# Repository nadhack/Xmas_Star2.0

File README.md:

Design files and documentation for the NADHack Xmas Star V2.0 as used in 
the SMD soldering workshop 2025.

* Addons - Addon files, source  and reference designs to enhance your stars.
* Docs - Assembly documentation greated using [MkDocs](https://www.mkdocs.org/)
* Hardware - [KiCad](https://www.kicad.org/) design files.

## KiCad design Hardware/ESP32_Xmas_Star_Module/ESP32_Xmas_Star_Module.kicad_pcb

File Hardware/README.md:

Hardware files for the NADHack Xmas Star V2.0.

* ESP32_Xmas_Star_Module - [KiCad](https://www.kicad.org/) design files.
* Jigs - Source and 3D print files for holding star PCB while applying solderpaste.

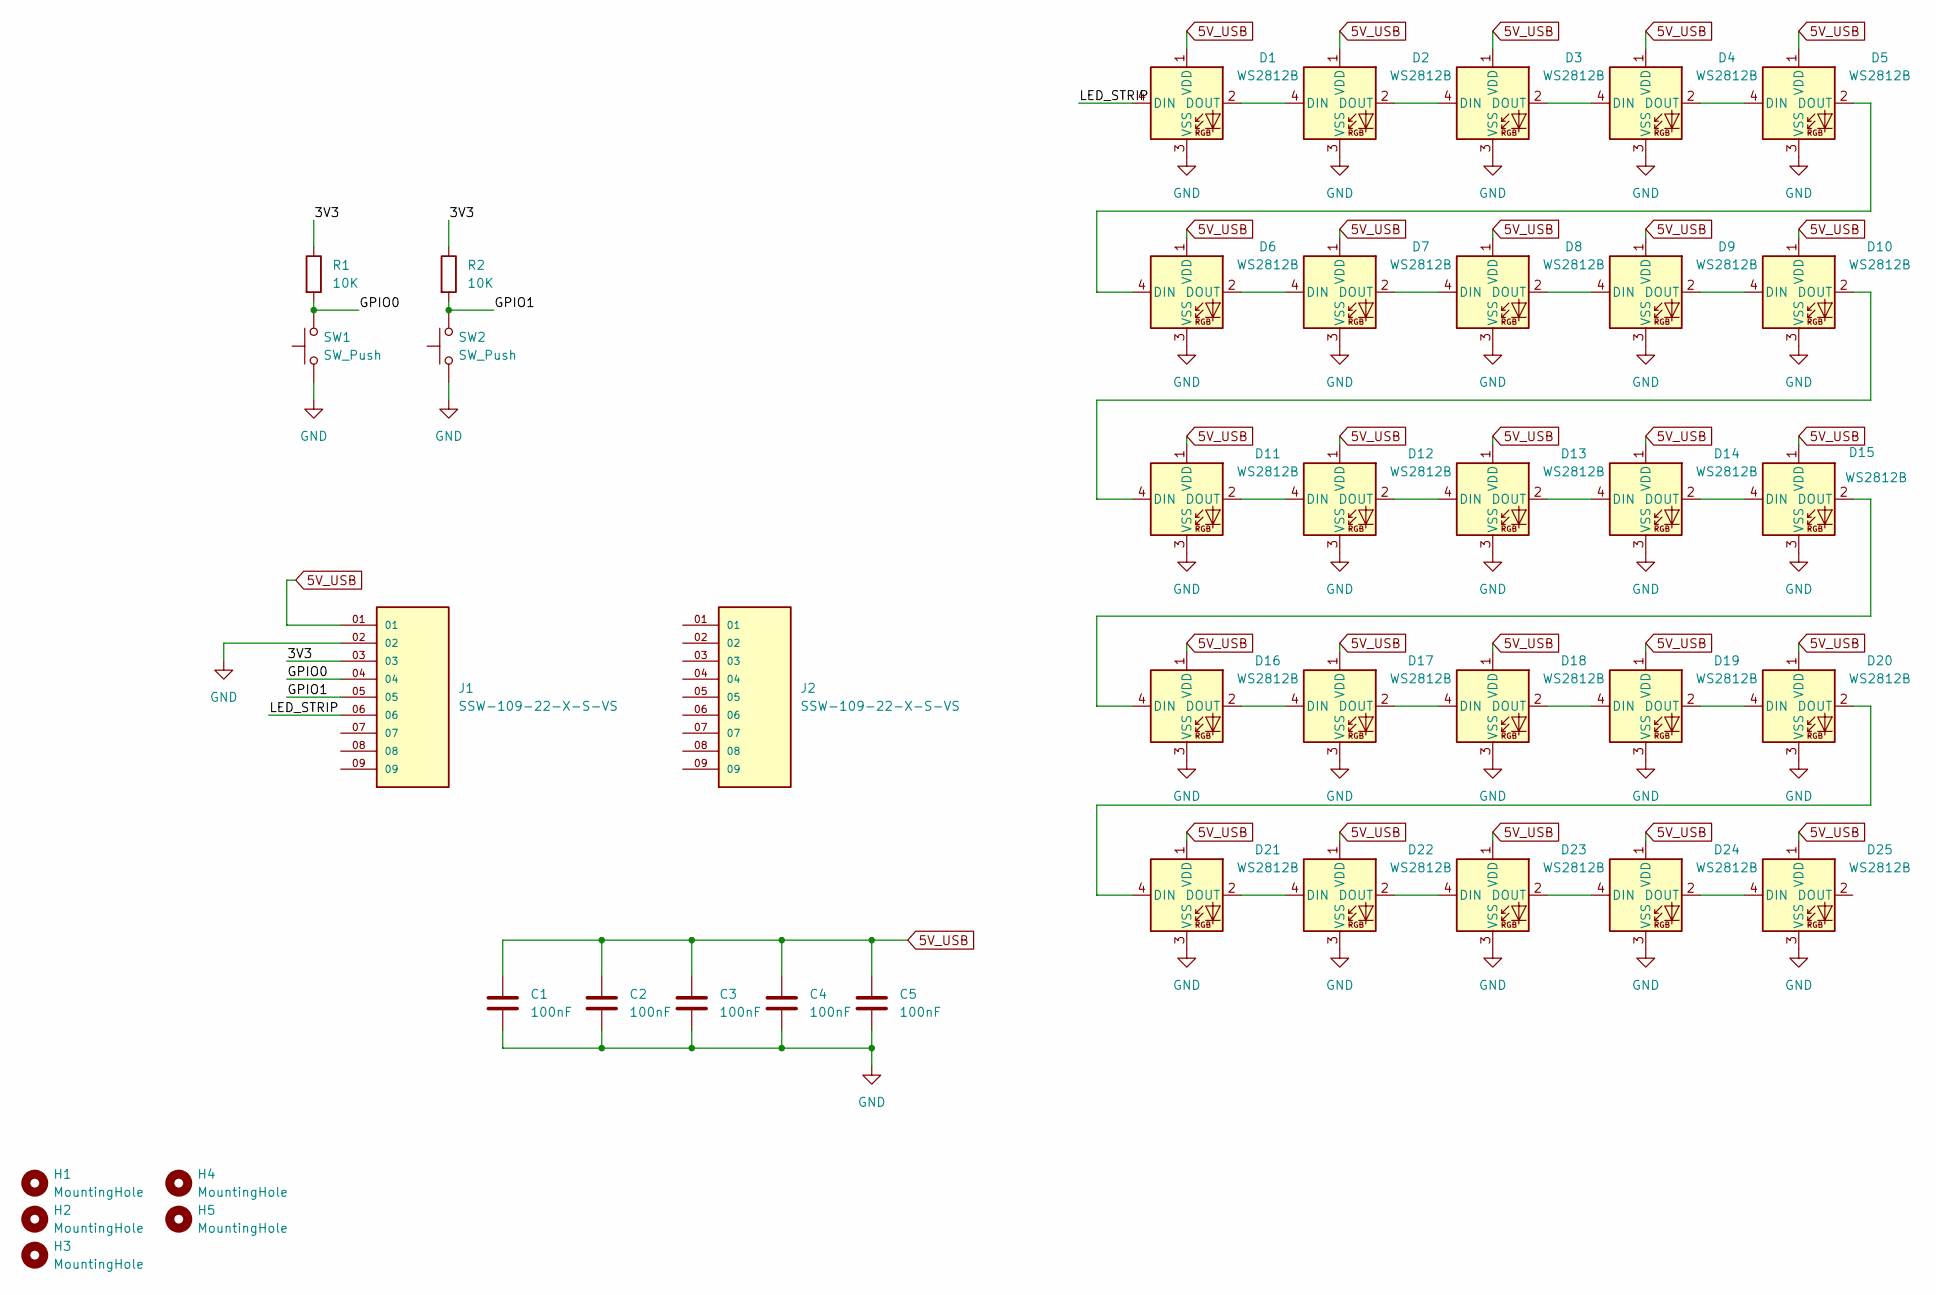
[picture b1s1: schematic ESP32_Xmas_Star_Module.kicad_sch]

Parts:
C1, C2, C3, C4, C5: 100nF; C_0805_2012Metric_Pad1.18x1.45mm_HandSolder
D1, D2, D3, D4, D5, D6, D7, D8, D9, D10, D11, D12, D13, D14, D15, D16, D17, D18, D19, D20, D21, D22, D23, D24, D25: WS2812B; LED_WS2812B_PLCC4_5.0x5.0mm_P3.2mm
H1, H2, H3, H4, H5: MountingHole; MountingHole_2.2mm_M2_Pad
J1, J2: SSW-109-22-X-S-VS; SAMTEC_SSW-109-22-X-S-VS; PARTREV B
R1, R2: 10K; R_0805_2012Metric_Pad1.20x1.40mm_HandSolder
SW1, SW2: SW_Push; SW_SPST_FSMSM

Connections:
5V_USB: C1.1, C2.1, C3.1, C4.1, C5.1, D1.1 (VDD), D2.1 (VDD), D3.1 (VDD), D4.1 (VDD), D5.1 (VDD), D6.1 (VDD), D7.1 (VDD), D8.1 (VDD), D9.1 (VDD), D10.1 (VDD), D11.1 (VDD), D12.1 (VDD), D13.1 (VDD), D14.1 (VDD), D15.1 (VDD), D16.1 (VDD), D17.1 (VDD), D18.1 (VDD), D19.1 (VDD), D20.1 (VDD), D21.1 (VDD), D22.1 (VDD), D23.1 (VDD), D24.1 (VDD), D25.1 (VDD), J1.01
/3V3: J1.03, R1.1, R2.1
/GPIO0: J1.04, R1.2, SW1.2
/GPIO1: J1.05, R2.2, SW2.2
/LED_STRIP: D1.4 (DIN), J1.06
GND: C1.2, C2.2, C3.2, C4.2, C5.2, D1.3 (VSS), D2.3 (VSS), D3.3 (VSS), D4.3 (VSS), D5.3 (VSS), D6.3 (VSS), D7.3 (VSS), D8.3 (VSS), D9.3 (VSS), D10.3 (VSS), D11.3 (VSS), D12.3 (VSS), D13.3 (VSS), D14.3 (VSS), D15.3 (VSS), D16.3 (VSS), D17.3 (VSS), D18.3 (VSS), D19.3 (VSS), D20.3 (VSS), D21.3 (VSS), D22.3 (VSS), D23.3 (VSS), D24.3 (VSS), D25.3 (VSS), J1.02, SW1.1, SW2.1
unnamed: D1.2 (DOUT), D2.4 (DIN)
unnamed: D2.2 (DOUT), D3.4 (DIN)
unnamed: D3.2 (DOUT), D4.4 (DIN)
unnamed: D4.2 (DOUT), D5.4 (DIN)
unnamed: D5.2 (DOUT), D6.4 (DIN)
unnamed: D6.2 (DOUT), D7.4 (DIN)
unnamed: D7.2 (DOUT), D8.4 (DIN)
unnamed: D8.2 (DOUT), D9.4 (DIN)
unnamed: D9.2 (DOUT), D10.4 (DIN)
unnamed: D10.2 (DOUT), D11.4 (DIN)
unnamed: D11.2 (DOUT), D12.4 (DIN)
unnamed: D12.2 (DOUT), D13.4 (DIN)
unnamed: D13.2 (DOUT), D14.4 (DIN)
unnamed: D14.2 (DOUT), D15.4 (DIN)
unnamed: D15.2 (DOUT), D16.4 (DIN)
unnamed: D16.2 (DOUT), D17.4 (DIN)
unnamed: D17.2 (DOUT), D18.4 (DIN)
unnamed: D18.2 (DOUT), D19.4 (DIN)
unnamed: D19.2 (DOUT), D20.4 (DIN)
unnamed: D20.2 (DOUT), D21.4 (DIN)
unnamed: D21.2 (DOUT), D22.4 (DIN)
unnamed: D22.2 (DOUT), D23.4 (DIN)
unnamed: D23.2 (DOUT), D24.4 (DIN)
unnamed: D24.2 (DOUT), D25.4 (DIN)

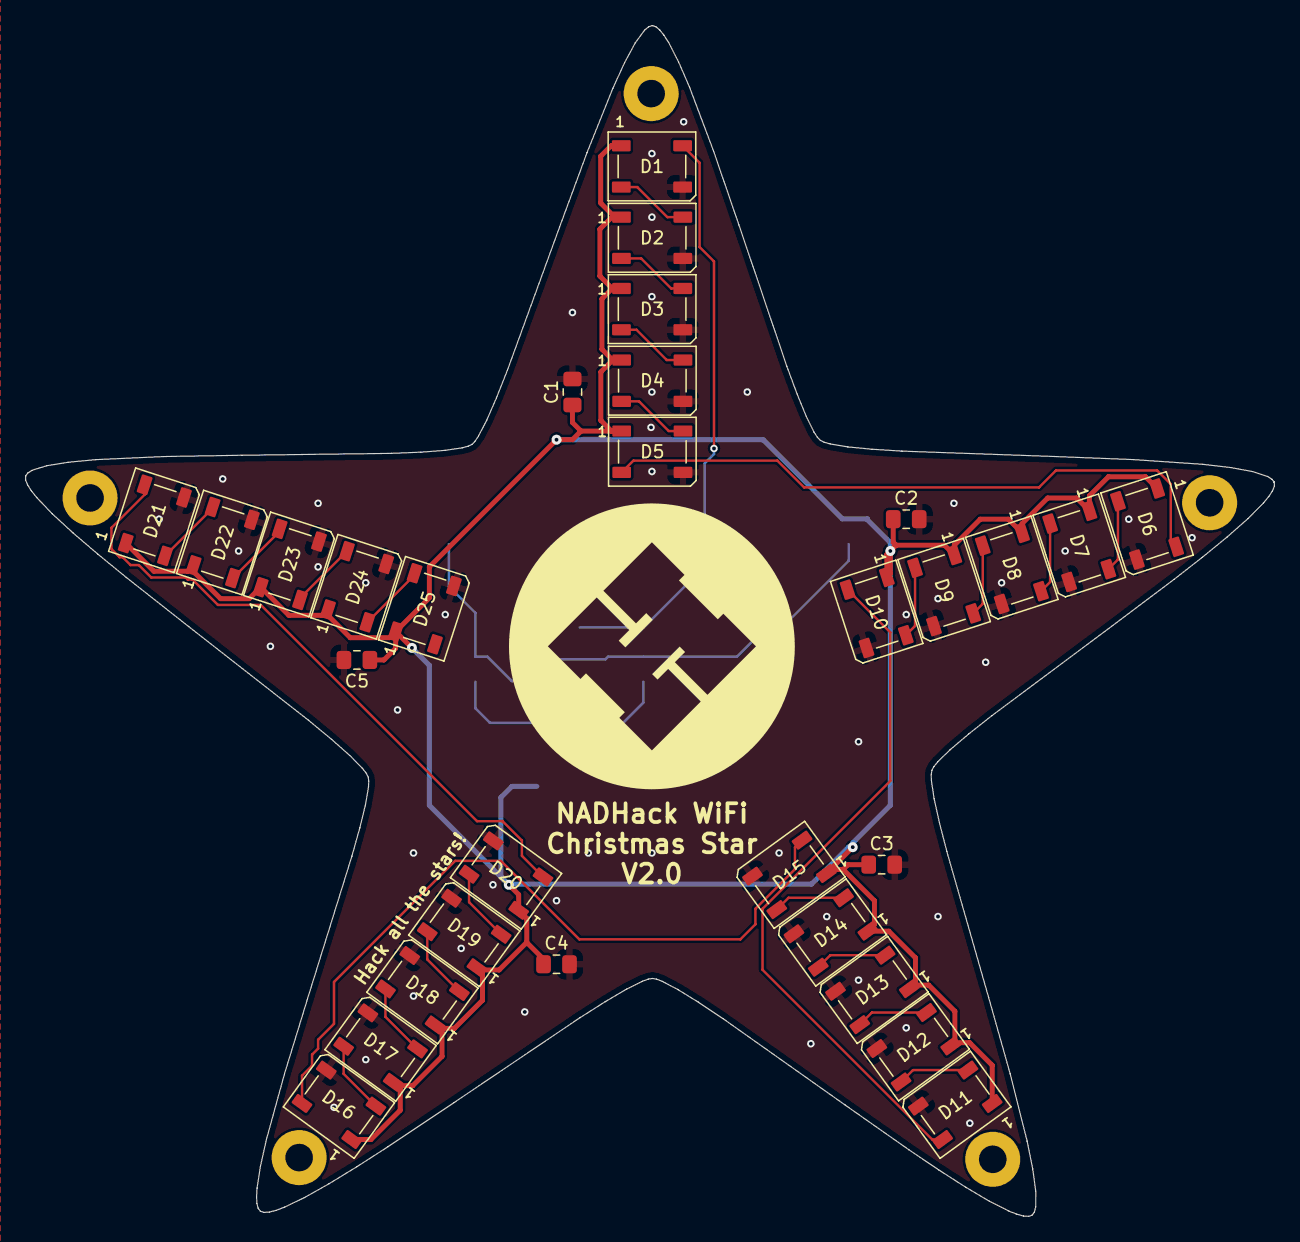
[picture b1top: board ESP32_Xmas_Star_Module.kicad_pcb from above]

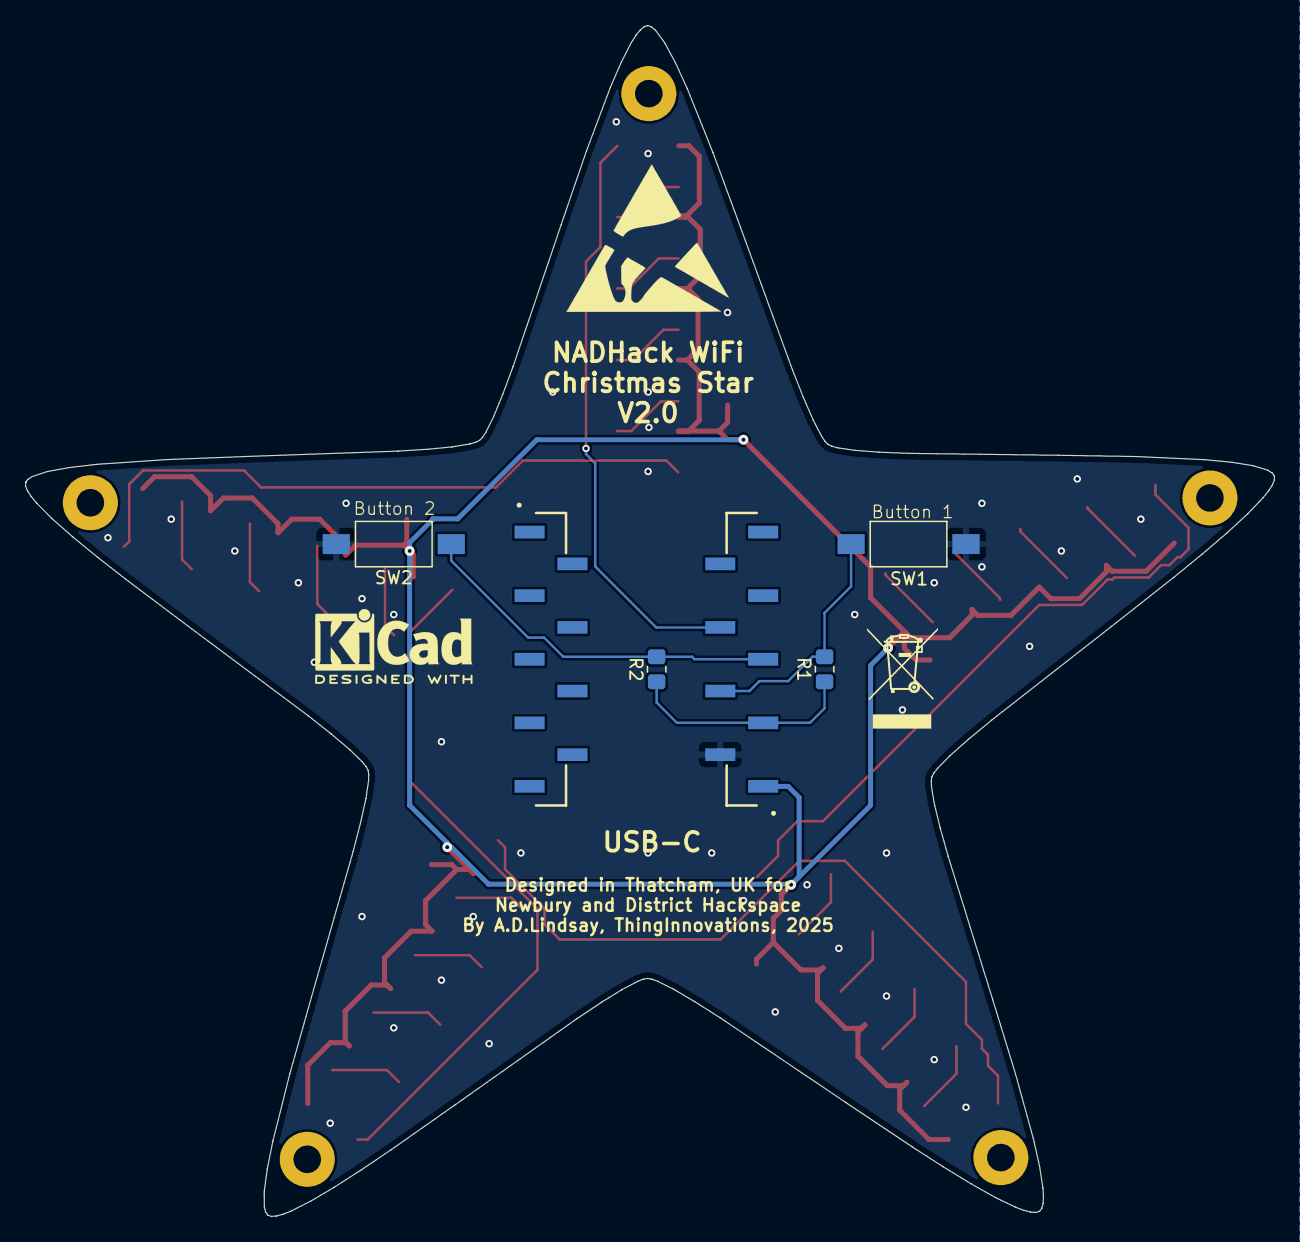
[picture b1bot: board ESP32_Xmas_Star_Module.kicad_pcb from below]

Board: 2 copper layers, 99.8 x 95.1 mm, 41 parts (6 on the bottom side), 30 nets.

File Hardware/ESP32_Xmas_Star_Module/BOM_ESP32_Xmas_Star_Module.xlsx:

Reference | Qty | Value | DNP | Footprint | Datasheet | Digi-Key Order | PiHut | Unit Cost | Line Cost
C1,C2,C3,C4,C5 | 5 | 100nF |  | Capacitor_SMD:C_0805_2012Metric_Pad1.18x1.45mm_HandSolder | ~ | 1276-1003-1-ND |  | 0.06 | 0.3
D1,D2,D3,D4,D5,D6,D7,D8,D9,D10,D11,D12,D13,D14,D15,D16,D17,D18,D19,D20,D21,D22,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 | 25 | WS2812B |  | LED_SMD:LED_WS2812B_PLCC4_5.0x5.0mm_P3.2mm | https://cdn-shop.adafruit.com/datasheets/WS2812B.pdf |  |  | 0.03 | 0.75
J1,J2 | 2 | SSW-109-22-X-S-VS |  | SSW-109-22-F-S-VS:SAMTEC_SSW-109-22-X-S-VS |  | SSW-109-22-F-S-VS-ND |  | 1.57 | 3.14
R1,R2 | 2 | 10K |  | Resistor_SMD:R_0805_2012Metric_Pad1.20x1.40mm_HandSolder | ~ | RMCF0805FT10K0CT-ND |  | 0.08 | 0.16
SW1,SW2 | 2 | SW |  | SWITCH TACTILE SPST-NO 0.05A 12V |  | 108-GSPTS004003CT-ND |  | 0.15 | 0.3
M1 | 1 | ESP32-C3-Mini |  | Waveshare ESP32-C3 Zero Mini Development Board | https://www.waveshare.com/wiki/ESP32-C3-Zero |  | WAV-25532 | 4.4000000000000004 | 4.4000000000000004
PCB | 1 |  |  | ESP32_XmasStarModV2 |  |  |  | 3.2 | 3.2
 |  |  |  |  |  |  |  |  | 12.25

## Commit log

2025-11-18 ESP32 based Xmas Star
    Version 2.0 using SMD LED
2025-11-18 Add documentation for NADHack Xmas Star V2.0
2025-11-23 Added documentation and addons
2025-11-24 Updates to configuration pages
2025-11-26 Update README with live site link
    Added a link to the live site in the README.
2025-11-26 Updates to Readme
2025-11-26 Add more details
2025-11-26 Tidy and updates to readme files
2025-11-26 fixed readme
2025-11-29 Tree topper adapter
    Use the star as a topper for your Christmas tree
2025-11-29 Add topper to readme
2025-11-30 Assembly guide updates
2025-12-01 Added details on alternative module
2025-12-09 Added starstick
2025-12-09 update image text
2025-12-09 Added fusion360 file
